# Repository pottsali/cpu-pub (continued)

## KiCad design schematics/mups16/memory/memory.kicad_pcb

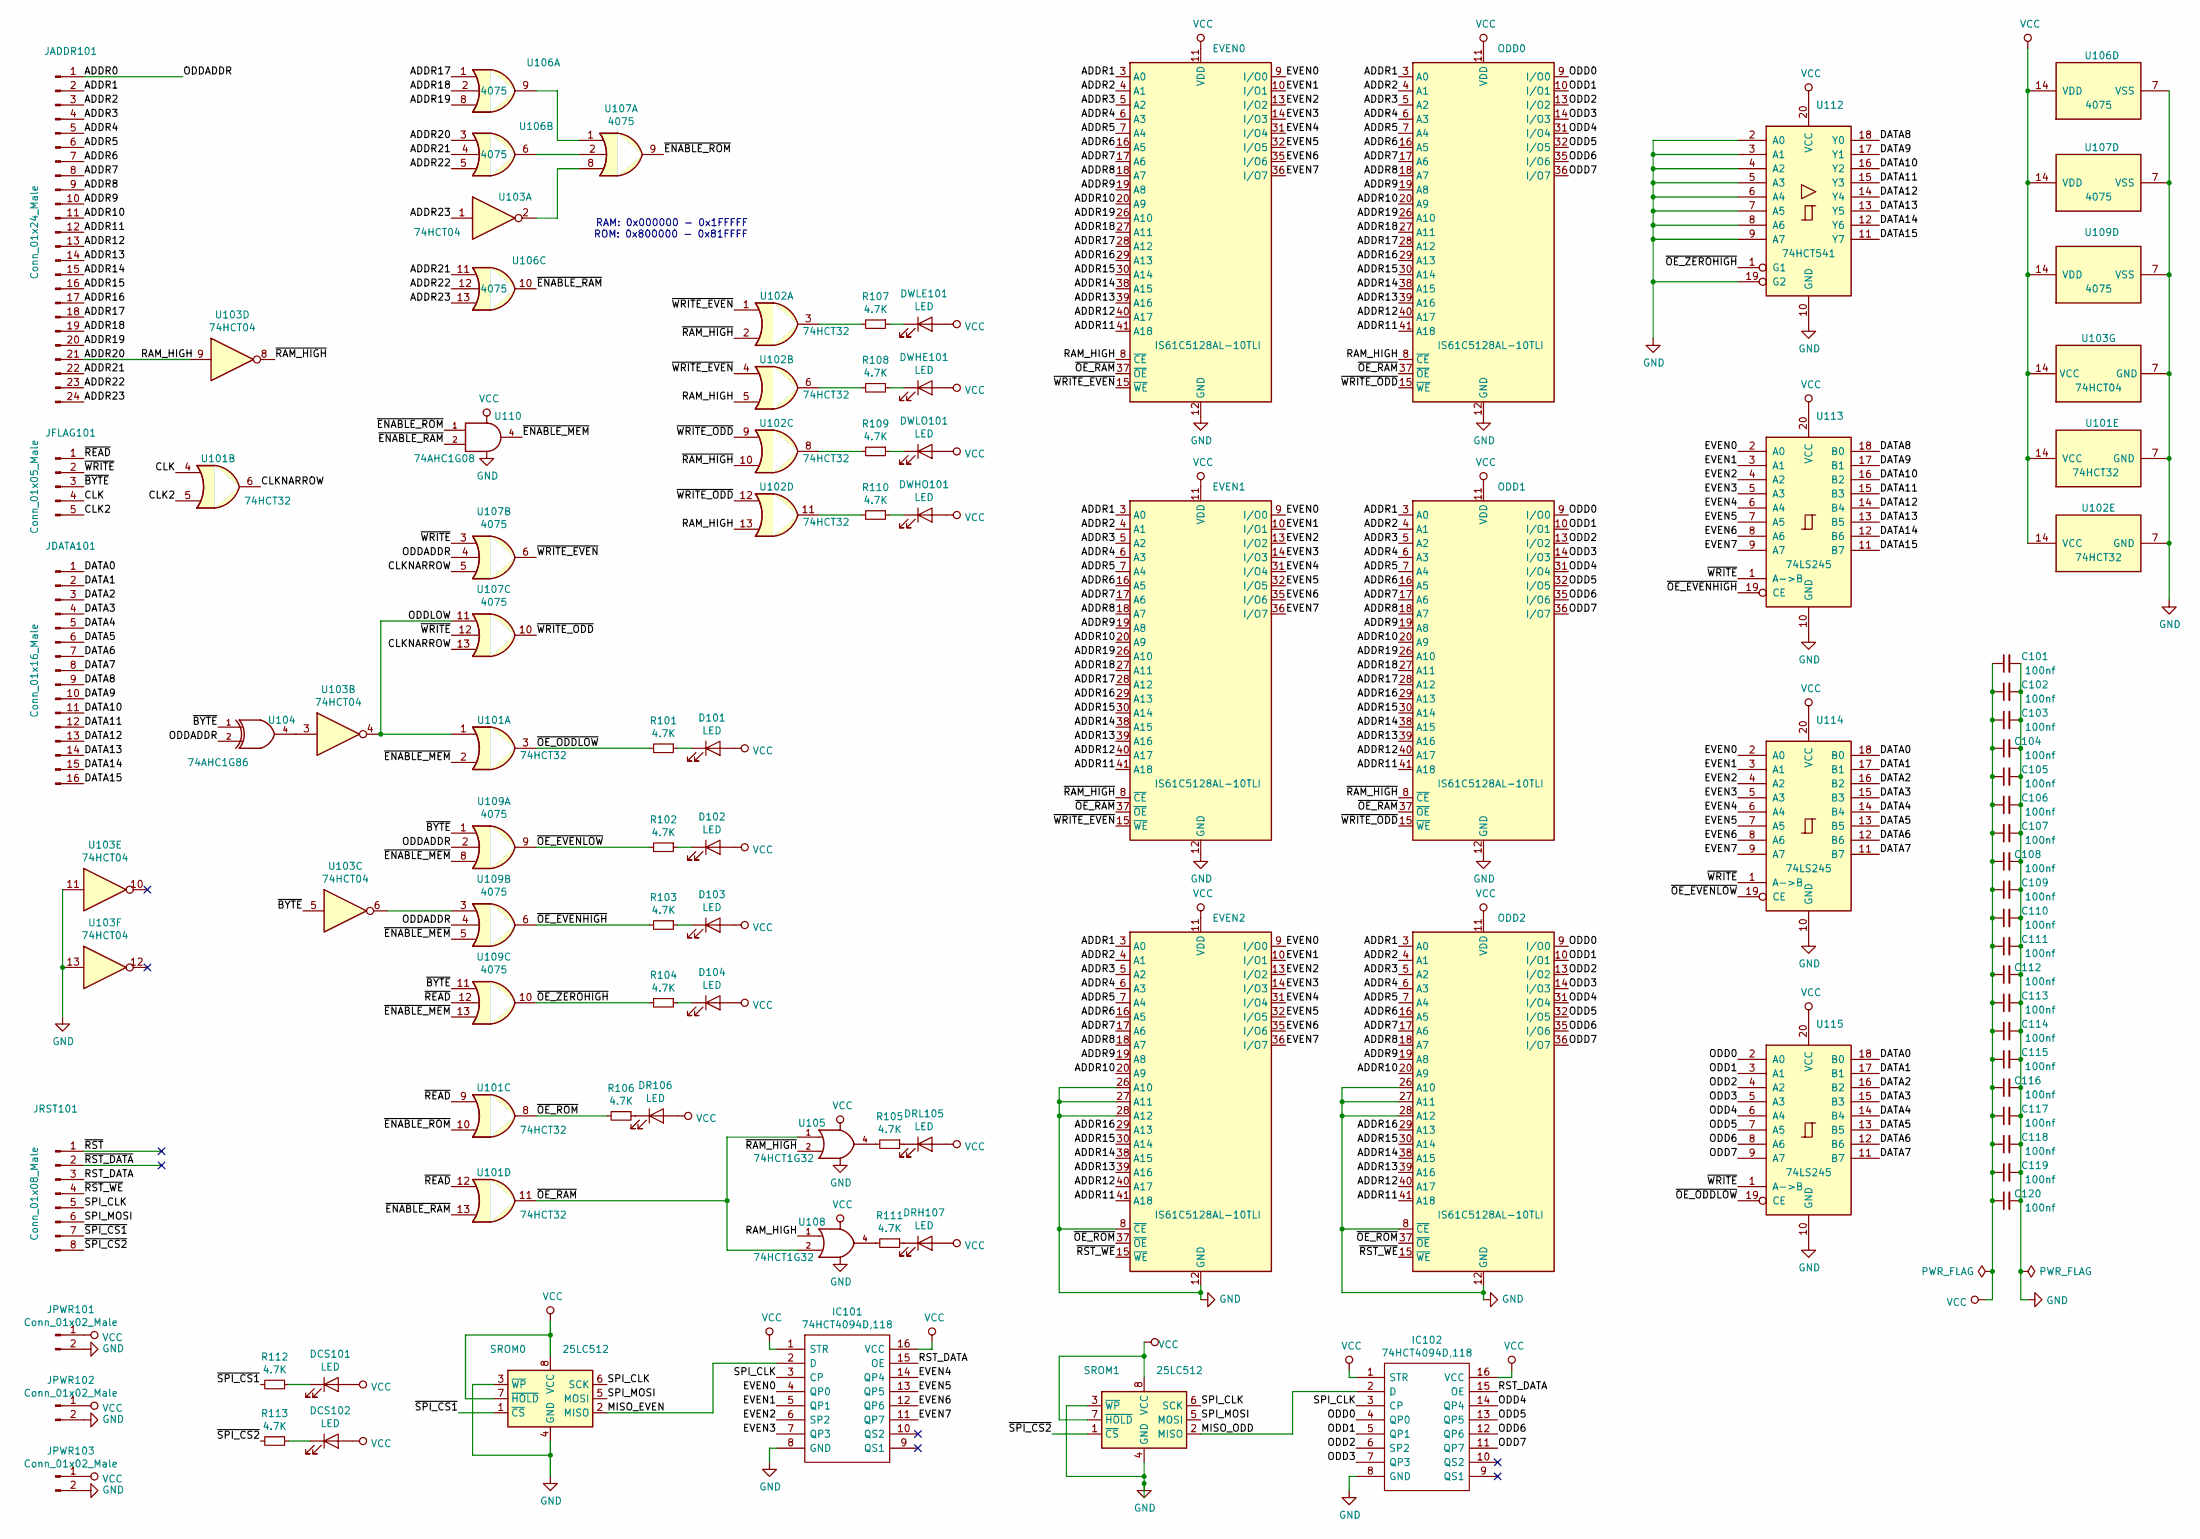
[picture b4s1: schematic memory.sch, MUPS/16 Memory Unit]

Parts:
C101, C102, C103, C104, C105, C106, C107, C108, C109, C110, C111, C112, C113, C114, C115, C116, C117, C118, C119, C120: 100nf; C_0805_2012Metric
D101, D102, D103, D104: LED; LED_0805_2012Metric
DCS101, DCS102: LED; LED_0805_2012Metric
DR106: LED; LED_0805_2012Metric
DRH107: LED; LED_0805_2012Metric
DRL105: LED; LED_0805_2012Metric
DWHE101: LED; LED_0805_2012Metric
DWHO101: LED; LED_0805_2012Metric
DWLE101: LED; LED_0805_2012Metric
DWLO101: LED; LED_0805_2012Metric
EVEN0, EVEN1, EVEN2: IS61C5128AL-10TLI; TSOP-II-44_10.16x18.41mm_P0.8mm
IC101, IC102: 74HCT4094D,118; SOIC127P600X175-16N; Mouser Part Number 771-74HCT4094D-T
JADDR101: Conn_01x24_Male; PinHeader_1x24_P2.54mm_Vertical
JDATA101: Conn_01x16_Male; PinHeader_1x16_P2.54mm_Vertical
JFLAG101: Conn_01x05_Male; PinHeader_1x05_P2.54mm_Vertical
JPWR101, JPWR102, JPWR103: Conn_01x02_Male; PinHeader_1x02_P2.54mm_Vertical
JRST101: Conn_01x08_Male; PinHeader_1x08_P2.54mm_Vertical
ODD0, ODD1, ODD2: IS61C5128AL-10TLI; TSOP-II-44_10.16x18.41mm_P0.8mm
R101, R102, R103, R104, R105, R106, R107, R108, R109, R110, R111, R112, R113: 4.7K; R_0805_2012Metric
SROM0, SROM1: 25LC512; SOIC-8_3.9x4.9mm_P1.27mm
U101, U102: 74HCT32; SOIC-14_3.9x8.7mm_P1.27mm
U103: 74HCT04; SOIC-14_3.9x8.7mm_P1.27mm
U104: 74AHC1G86; TSOP-5_1.65x3.05mm_P0.95mm
U105, U108: 74HCT1G32; TSOP-5_1.65x3.05mm_P0.95mm
U106, U107, U109: 4075; SOIC-14_3.9x8.7mm_P1.27mm
U110: 74AHC1G08; TSOP-5_1.65x3.05mm_P0.95mm
U112: 74HCT541; SO-20_12.8x7.5mm_P1.27mm
U113, U114, U115: 74LS245; SO-20_12.8x7.5mm_P1.27mm

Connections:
/ADDR0: JADDR101.1, U104.2, U107.4, U109.2, U109.4
/ADDR1: EVEN0.3 (A0), EVEN1.3 (A0), EVEN2.3 (A0), JADDR101.2, ODD0.3 (A0), ODD1.3 (A0), ODD2.3 (A0)
/ADDR2: EVEN0.4 (A1), EVEN1.4 (A1), EVEN2.4 (A1), JADDR101.3, ODD0.4 (A1), ODD1.4 (A1), ODD2.4 (A1)
/ADDR3: EVEN0.5 (A2), EVEN1.5 (A2), EVEN2.5 (A2), JADDR101.4, ODD0.5 (A2), ODD1.5 (A2), ODD2.5 (A2)
/ADDR4: EVEN0.6 (A3), EVEN1.6 (A3), EVEN2.6 (A3), JADDR101.5, ODD0.6 (A3), ODD1.6 (A3), ODD2.6 (A3)
/ADDR5: EVEN0.7 (A4), EVEN1.7 (A4), EVEN2.7 (A4), JADDR101.6, ODD0.7 (A4), ODD1.7 (A4), ODD2.7 (A4)
/ADDR6: EVEN0.16 (A5), EVEN1.16 (A5), EVEN2.16 (A5), JADDR101.7, ODD0.16 (A5), ODD1.16 (A5), ODD2.16 (A5)
/ADDR7: EVEN0.17 (A6), EVEN1.17 (A6), EVEN2.17 (A6), JADDR101.8, ODD0.17 (A6), ODD1.17 (A6), ODD2.17 (A6)
/ADDR8: EVEN0.18 (A7), EVEN1.18 (A7), EVEN2.18 (A7), JADDR101.9, ODD0.18 (A7), ODD1.18 (A7), ODD2.18 (A7)
/ADDR9: EVEN0.19 (A8), EVEN1.19 (A8), EVEN2.19 (A8), JADDR101.10, ODD0.19 (A8), ODD1.19 (A8), ODD2.19 (A8)
/ADDR10: EVEN0.20 (A9), EVEN1.20 (A9), EVEN2.20 (A9), JADDR101.11, ODD0.20 (A9), ODD1.20 (A9), ODD2.20 (A9)
/ADDR11: EVEN0.41 (A18), EVEN1.41 (A18), EVEN2.41 (A18), JADDR101.12, ODD0.41 (A18), ODD1.41 (A18), ODD2.41 (A18)
/ADDR12: EVEN0.40 (A17), EVEN1.40 (A17), EVEN2.40 (A17), JADDR101.13, ODD0.40 (A17), ODD1.40 (A17), ODD2.40 (A17)
/ADDR13: EVEN0.39 (A16), EVEN1.39 (A16), EVEN2.39 (A16), JADDR101.14, ODD0.39 (A16), ODD1.39 (A16), ODD2.39 (A16)
/ADDR14: EVEN0.38 (A15), EVEN1.38 (A15), EVEN2.38 (A15), JADDR101.15, ODD0.38 (A15), ODD1.38 (A15), ODD2.38 (A15)
/ADDR15: EVEN0.30 (A14), EVEN1.30 (A14), EVEN2.30 (A14), JADDR101.16, ODD0.30 (A14), ODD1.30 (A14), ODD2.30 (A14)
/ADDR16: EVEN0.29 (A13), EVEN1.29 (A13), EVEN2.29 (A13), JADDR101.17, ODD0.29 (A13), ODD1.29 (A13), ODD2.29 (A13)
/ADDR17: EVEN0.28 (A12), EVEN1.28 (A12), JADDR101.18, ODD0.28 (A12), ODD1.28 (A12), U106.1
/ADDR18: EVEN0.27 (A11), EVEN1.27 (A11), JADDR101.19, ODD0.27 (A11), ODD1.27 (A11), U106.2
/ADDR19: EVEN0.26 (A10), EVEN1.26 (A10), JADDR101.20, ODD0.26 (A10), ODD1.26 (A10), U106.8
/ADDR20: EVEN0.8 (~CE), JADDR101.21, ODD0.8 (~CE), U102.5, U102.13, U103.9, U106.3, U108.1
/ADDR21: JADDR101.22, U106.4, U106.11
/ADDR22: JADDR101.23, U106.5, U106.12
/ADDR23: JADDR101.24, U103.1, U106.13
/CLK: JFLAG101.4, U101.4
/CLK2: JFLAG101.5, U101.5
/CLKNARROW: U101.6, U107.5, U107.13
/DATA0: JDATA101.1, U114.18 (B0), U115.18 (B0)
/DATA1: JDATA101.2, U114.17 (B1), U115.17 (B1)
/DATA2: JDATA101.3, U114.16 (B2), U115.16 (B2)
/DATA3: JDATA101.4, U114.15 (B3), U115.15 (B3)
/DATA4: JDATA101.5, U114.14 (B4), U115.14 (B4)
/DATA5: JDATA101.6, U114.13 (B5), U115.13 (B5)
/DATA6: JDATA101.7, U114.12 (B6), U115.12 (B6)
/DATA7: JDATA101.8, U114.11 (B7), U115.11 (B7)
/DATA8: JDATA101.9, U112.18 (Y0), U113.18 (B0)
/DATA9: JDATA101.10, U112.17 (Y1), U113.17 (B1)
/DATA10: JDATA101.11, U112.16 (Y2), U113.16 (B2)
/DATA11: JDATA101.12, U112.15 (Y3), U113.15 (B3)
/DATA12: JDATA101.13, U112.14 (Y4), U113.14 (B4)
/DATA13: JDATA101.14, U112.13 (Y5), U113.13 (B5)
/DATA14: JDATA101.15, U112.12 (Y6), U113.12 (B6)
/DATA15: JDATA101.16, U112.11 (Y7), U113.11 (B7)
/EVEN0: EVEN0.9 (I/O0), EVEN1.9 (I/O0), EVEN2.9 (I/O0), IC101.4 (QP0), U113.2 (A0), U114.2 (A0)
/EVEN1: EVEN0.10 (I/O1), EVEN1.10 (I/O1), EVEN2.10 (I/O1), IC101.5 (QP1), U113.3 (A1), U114.3 (A1)
/EVEN2: EVEN0.13 (I/O2), EVEN1.13 (I/O2), EVEN2.13 (I/O2), IC101.6 (SP2), U113.4 (A2), U114.4 (A2)
/EVEN3: EVEN0.14 (I/O3), EVEN1.14 (I/O3), EVEN2.14 (I/O3), IC101.7 (QP3), U113.5 (A3), U114.5 (A3)
/EVEN4: EVEN0.31 (I/O4), EVEN1.31 (I/O4), EVEN2.31 (I/O4), IC101.14 (QP4), U113.6 (A4), U114.6 (A4)
/EVEN5: EVEN0.32 (I/O5), EVEN1.32 (I/O5), EVEN2.32 (I/O5), IC101.13 (QP5), U113.7 (A5), U114.7 (A5)
/EVEN6: EVEN0.35 (I/O6), EVEN1.35 (I/O6), EVEN2.35 (I/O6), IC101.12 (QP6), U113.8 (A6), U114.8 (A6)
/EVEN7: EVEN0.36 (I/O7), EVEN1.36 (I/O7), EVEN2.36 (I/O7), IC101.11 (QP7), U113.9 (A7), U114.9 (A7)
/MISO_EVEN: IC101.2 (D), SROM0.2 (MISO)
/MISO_ODD: IC102.2 (D), SROM1.2 (MISO)
/ODD0: IC102.4 (QP0), ODD0.9 (I/O0), ODD1.9 (I/O0), ODD2.9 (I/O0), U115.2 (A0)
/ODD1: IC102.5 (QP1), ODD0.10 (I/O1), ODD1.10 (I/O1), ODD2.10 (I/O1), U115.3 (A1)
/ODD2: IC102.6 (SP2), ODD0.13 (I/O2), ODD1.13 (I/O2), ODD2.13 (I/O2), U115.4 (A2)
/ODD3: IC102.7 (QP3), ODD0.14 (I/O3), ODD1.14 (I/O3), ODD2.14 (I/O3), U115.5 (A3)
/ODD4: IC102.14 (QP4), ODD0.31 (I/O4), ODD1.31 (I/O4), ODD2.31 (I/O4), U115.6 (A4)
/ODD5: IC102.13 (QP5), ODD0.32 (I/O5), ODD1.32 (I/O5), ODD2.32 (I/O5), U115.7 (A5)
/ODD6: IC102.12 (QP6), ODD0.35 (I/O6), ODD1.35 (I/O6), ODD2.35 (I/O6), U115.8 (A6)
/ODD7: IC102.11 (QP7), ODD0.36 (I/O7), ODD1.36 (I/O7), ODD2.36 (I/O7), U115.9 (A7)
/ODDLOW: U101.1, U103.4, U107.11
/RST_DATA: IC101.15 (OE), IC102.15 (OE), JRST101.3
/SPI_CLK: IC101.3 (CP), IC102.3 (CP), JRST101.5, SROM0.6 (SCK), SROM1.6 (SCK)
/SPI_MOSI: JRST101.6, SROM0.5 (MOSI), SROM1.5 (MOSI)
/~: U103.6, U109.3
/~BYTE: JFLAG101.3, U103.5, U104.1, U109.1, U109.11
/~ENABLE_MEM: U101.2, U109.5, U109.8, U109.13, U110.4
/~ENABLE_RAM: U101.13, U106.10, U110.2
/~ENABLE_ROM: U101.10, U107.9, U110.1
/~OE_EVENHIGH: R103.2, U109.6, U113.19 (CE)
/~OE_EVENLOW: R102.2, U109.9, U114.19 (CE)
/~OE_ODDLOW: R101.2, U101.3, U115.19 (CE)
/~OE_RAM: EVEN0.37 (~OE), EVEN1.37 (~OE), ODD0.37 (~OE), ODD1.37 (~OE), U101.11, U105.1, U108.2
/~OE_ROM: EVEN2.37 (~OE), ODD2.37 (~OE), R106.2, U101.8
/~OE_ZEROHIGH: R104.2, U109.10, U112.1 (G1)
/~RAM_HIGH: EVEN1.8 (~CE), ODD1.8 (~CE), U102.2, U102.10, U103.8, U105.2
/~READ: JFLAG101.1, U101.9, U101.12, U109.12
/~RST: JRST101.1
/~RST_DATA: JRST101.2
/~RST_WE: EVEN2.15 (~WE), JRST101.4, ODD2.15 (~WE)
/~SPI_CS1: JRST101.7, R112.2, SROM0.1 (~CS)
/~SPI_CS2: JRST101.8, R113.2, SROM1.1 (~CS)
/~WRITE: JFLAG101.2, U107.3, U107.12, U113.1 (A->B), U114.1 (A->B), U115.1 (A->B)
/~WRITE_EVEN: EVEN0.15 (~WE), EVEN1.15 (~WE), U102.1, U102.4, U107.6
/~WRITE_ODD: ODD0.15 (~WE), ODD1.15 (~WE), U102.9, U102.12, U107.10
GND: C101.2, C102.2, C103.2, C104.2, C105.2, C106.2, C107.2, C108.2, C109.2, C110.2, C111.2, C112.2, C113.2, C114.2, C115.2, C116.2, C117.2, C118.2, C119.2, C120.2, EVEN0.12 (GND), EVEN0.34 (GND), EVEN1.12 (GND), EVEN1.34 (GND), EVEN2.8 (~CE), EVEN2.12 (GND), EVEN2.26 (A10), EVEN2.27 (A11), EVEN2.28 (A12), EVEN2.34 (GND), IC101.8 (GND), IC102.8 (GND), JPWR101.2, JPWR102.2, JPWR103.2, ODD0.12 (GND), ODD0.34 (GND), ODD1.12 (GND), ODD1.34 (GND), ODD2.8 (~CE), ODD2.12 (GND), ODD2.26 (A10), ODD2.27 (A11), ODD2.28 (A12), ODD2.34 (GND), SROM0.3 (~WP), SROM0.4 (GND), SROM1.3 (~WP), SROM1.4 (GND), U101.7 (GND), U102.7 (GND), U103.7 (GND), U103.11, U103.13, U104.3 (GND), U105.3 (GND), U106.7 (VSS), U107.7 (VSS), U108.3 (GND), U109.7 (VSS), U110.3 (GND), U112.2 (A0), U112.3 (A1), U112.4 (A2), U112.5 (A3), U112.6 (A4), U112.7 (A5), U112.8 (A6), U112.9 (A7), U112.10 (GND), U112.19 (G2), U113.10 (GND), U114.10 (GND), U115.10 (GND)
unnamed: D101.1 (K), R101.1
unnamed: D102.1 (K), R102.1
unnamed: D103.1 (K), R103.1
unnamed: D104.1 (K), R104.1
unnamed: DCS101.1 (K), R112.1
unnamed: DCS102.1 (K), R113.1
unnamed: DR106.1 (K), R106.1
unnamed: DRH107.1 (K), R111.1
unnamed: DRL105.1 (K), R105.1
unnamed: DWHE101.1 (K), R108.1
unnamed: DWHO101.1 (K), R110.1
unnamed: DWLE101.1 (K), R107.1
unnamed: DWLO101.1 (K), R109.1
unnamed: R105.2, U105.4
unnamed: R107.2, U102.3
unnamed: R108.2, U102.6
unnamed: R109.2, U102.8
unnamed: R110.2, U102.11
unnamed: R111.2, U108.4
unnamed: U103.2, U107.8
unnamed: U103.3, U104.4
unnamed: U106.6, U107.2
unnamed: U106.9, U107.1
VCC: C101.1, C102.1, C103.1, C104.1, C105.1, C106.1, C107.1, C108.1, C109.1, C110.1, C111.1, C112.1, C113.1, C114.1, C115.1, C116.1, C117.1, C118.1, C119.1, C120.1, D101.2 (A), D102.2 (A), D103.2 (A), D104.2 (A), DCS101.2 (A), DCS102.2 (A), DR106.2 (A), DRH107.2 (A), DRL105.2 (A), DWHE101.2 (A), DWHO101.2 (A), DWLE101.2 (A), DWLO101.2 (A), EVEN0.11 (VDD), EVEN0.33 (VDD), EVEN1.11 (VDD), EVEN1.33 (VDD), EVEN2.11 (VDD), EVEN2.33 (VDD), IC101.1 (STR), IC101.16 (VCC), IC102.1 (STR), IC102.16 (VCC), JPWR101.1, JPWR102.1, JPWR103.1, ODD0.11 (VDD), ODD0.33 (VDD), ODD1.11 (VDD), ODD1.33 (VDD), ODD2.11 (VDD), ODD2.33 (VDD), SROM0.7 (~HOLD), SROM0.8 (VCC), SROM1.7 (~HOLD), SROM1.8 (VCC), U101.14 (VCC), U102.14 (VCC), U103.14 (VCC), U104.5 (VCC), U105.5 (VCC), U106.14 (VDD), U107.14 (VDD), U108.5 (VCC), U109.14 (VDD), U110.5 (VCC), U112.20 (VCC), U113.20 (VCC), U114.20 (VCC), U115.20 (VCC)

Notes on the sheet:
RAM: 0x000000 - 0x1FFFFF ROM: 0x800000 - 0x81FFFF

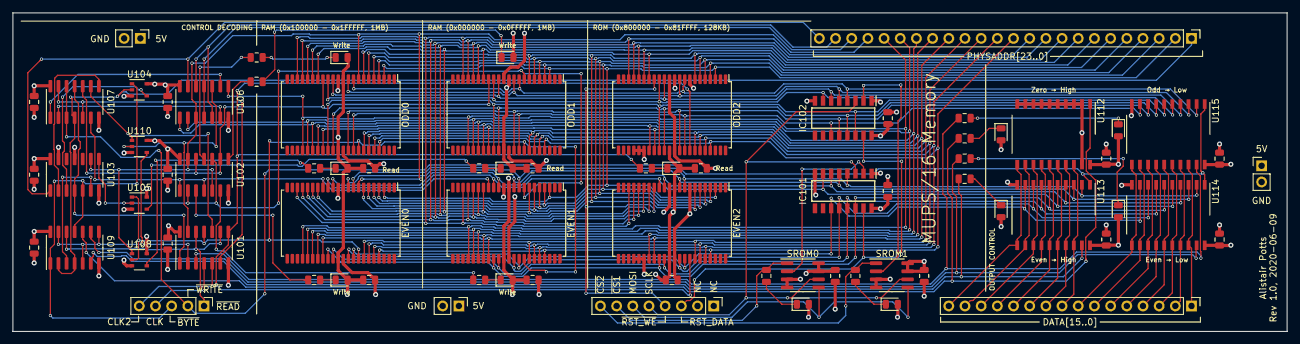
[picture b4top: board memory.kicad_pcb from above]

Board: 4 copper layers, 200.0 x 50.0 mm, 77 parts (0 on the bottom side), 109 nets.

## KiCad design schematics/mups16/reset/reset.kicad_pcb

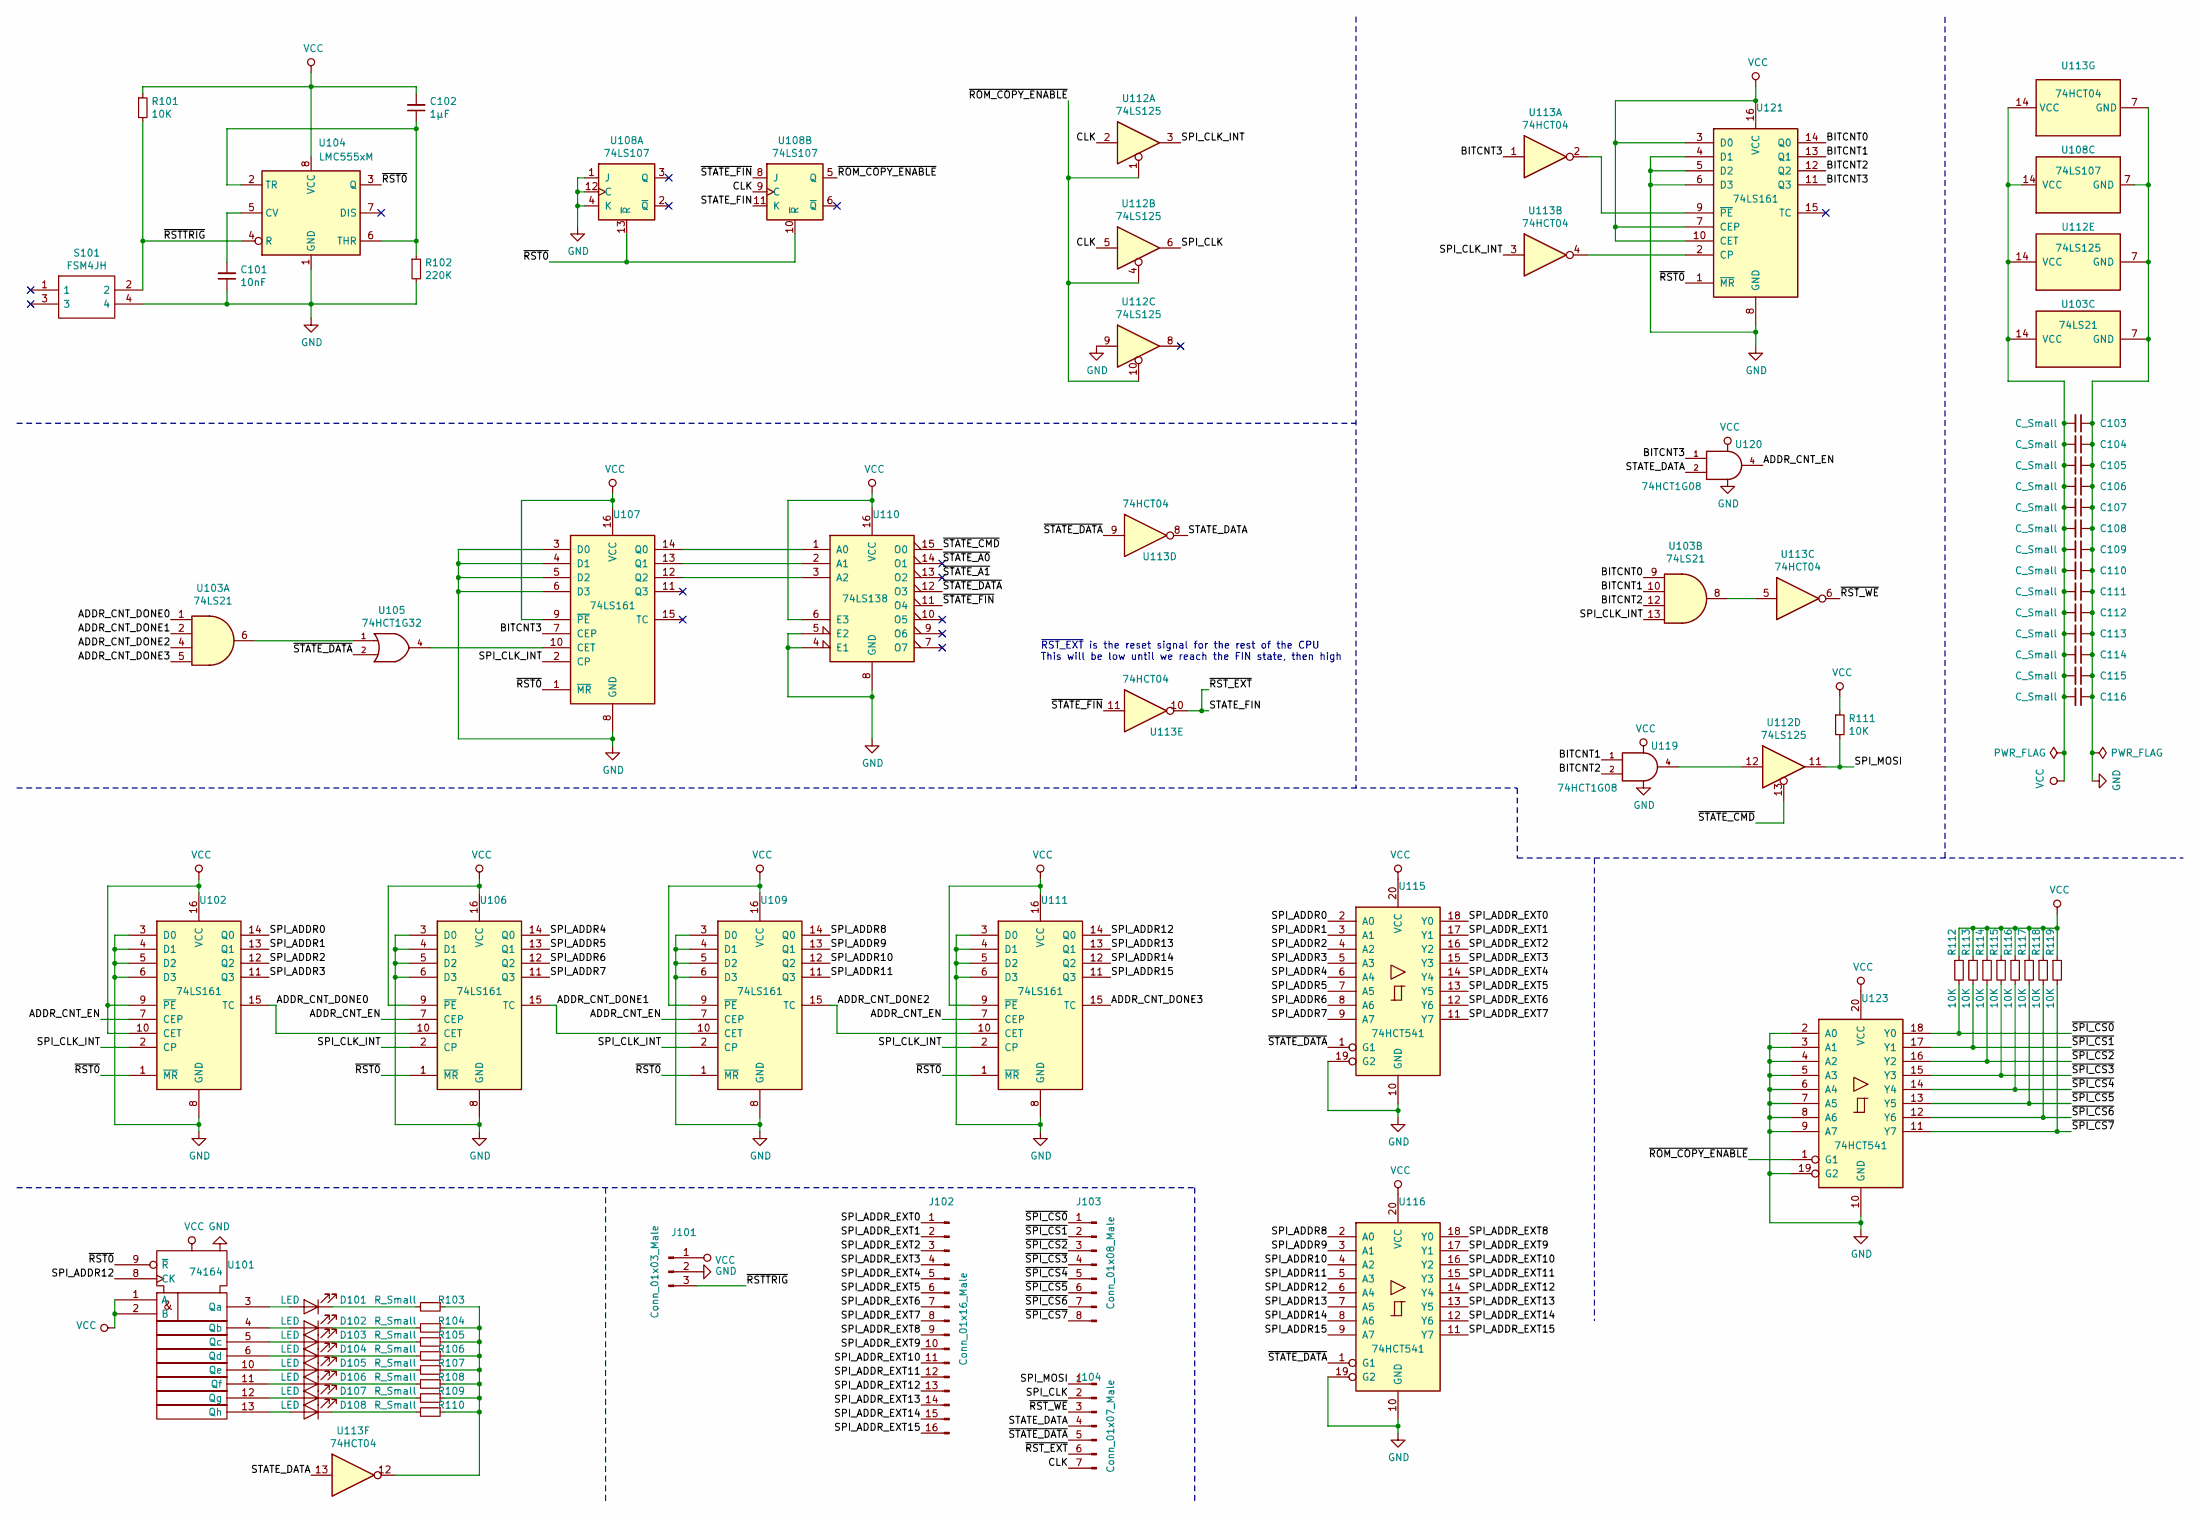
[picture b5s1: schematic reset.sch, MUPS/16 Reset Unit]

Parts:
C101: 10nF; C_0805_2012Metric
C102: 1μF; C_0805_2012Metric
C103, C104, C105, C106, C107, C108, C109, C110, C111, C112, C113, C114, C115, C116: C_Small; C_0805_2012Metric
D101, D102, D103, D104, D105, D106, D107, D108: LED; LED_0805_2012Metric
J101: Conn_01x03_Male; PinHeader_1x03_P2.54mm_Vertical
J102: Conn_01x16_Male; PinHeader_1x16_P2.54mm_Vertical
J103: Conn_01x08_Male; PinHeader_1x08_P2.54mm_Vertical
J104: Conn_01x07_Male; PinHeader_1x07_P2.54mm_Vertical
R101, R111, R112, R113, R114, R115, R116, R117, R118, R119: 10K; R_0805_2012Metric
R102: 220K; R_0805_2012Metric
R103, R104, R105, R106, R107, R108, R109, R110: R_Small; R_0805_2012Metric
S101: FSM4JH; Mouser Part Number 506-FSM4JH
U101: 74164; SOIC-14_3.9x8.7mm_P1.27mm
U102, U106, U107, U109, U111, U121: 74LS161; SOIC-16_3.9x9.9mm_P1.27mm
U103: 74LS21; SOIC-14_3.9x8.7mm_P1.27mm
U104: LMC555xM; SOIC-8_3.9x4.9mm_P1.27mm
U105: 74HCT1G32; TSOP-5_1.65x3.05mm_P0.95mm
U108: 74LS107; SOIC-14_3.9x8.7mm_P1.27mm
U110: 74LS138; SOIC-16_3.9x9.9mm_P1.27mm
U112: 74LS125; SOIC-14_3.9x8.7mm_P1.27mm
U113: 74HCT04; SOIC-14_3.9x8.7mm_P1.27mm
U115, U116, U123: 74HCT541; SO-20_12.8x7.5mm_P1.27mm
U119, U120: 74HCT1G08; TSOP-5_1.65x3.05mm_P0.95mm

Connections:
/ADDR_CNT_DONE0: U102.15 (TC), U103.1, U106.10 (CET)
/ADDR_CNT_DONE1: U103.2, U106.15 (TC), U109.10 (CET)
/ADDR_CNT_DONE2: U103.4, U109.15 (TC), U111.10 (CET)
/ADDR_CNT_DONE3: U103.5, U111.15 (TC)
/ADDR_CNT_EN: U102.7 (CEP), U106.7 (CEP), U109.7 (CEP), U111.7 (CEP), U120.4
/BITCNT0: U103.9, U121.14 (Q0)
/BITCNT1: U103.10, U119.1, U121.13 (Q1)
/BITCNT2: U103.12, U119.2, U121.12 (Q2)
/BITCNT3: U107.7 (CEP), U113.1, U120.1, U121.11 (Q3)
/CLK: J104.7, U108.9 (C), U112.2, U112.5
/SPI_ADDR0: U102.14 (Q0), U115.2 (A0)
/SPI_ADDR1: U102.13 (Q1), U115.3 (A1)
/SPI_ADDR2: U102.12 (Q2), U115.4 (A2)
/SPI_ADDR3: U102.11 (Q3), U115.5 (A3)
/SPI_ADDR4: U106.14 (Q0), U115.6 (A4)
/SPI_ADDR5: U106.13 (Q1), U115.7 (A5)
/SPI_ADDR6: U106.12 (Q2), U115.8 (A6)
/SPI_ADDR7: U106.11 (Q3), U115.9 (A7)
/SPI_ADDR8: U109.14 (Q0), U116.2 (A0)
/SPI_ADDR9: U109.13 (Q1), U116.3 (A1)
/SPI_ADDR10: U109.12 (Q2), U116.4 (A2)
/SPI_ADDR11: U109.11 (Q3), U116.5 (A3)
/SPI_ADDR12: U101.8 (CK), U111.14 (Q0), U116.6 (A4)
/SPI_ADDR13: U111.13 (Q1), U116.7 (A5)
/SPI_ADDR14: U111.12 (Q2), U116.8 (A6)
/SPI_ADDR15: U111.11 (Q3), U116.9 (A7)
/SPI_ADDR_EXT0: J102.1, U115.18 (Y0)
/SPI_ADDR_EXT1: J102.2, U115.17 (Y1)
/SPI_ADDR_EXT2: J102.3, U115.16 (Y2)
/SPI_ADDR_EXT3: J102.4, U115.15 (Y3)
/SPI_ADDR_EXT4: J102.5, U115.14 (Y4)
/SPI_ADDR_EXT5: J102.6, U115.13 (Y5)
/SPI_ADDR_EXT6: J102.7, U115.12 (Y6)
/SPI_ADDR_EXT7: J102.8, U115.11 (Y7)
/SPI_ADDR_EXT8: J102.9, U116.18 (Y0)
/SPI_ADDR_EXT9: J102.10, U116.17 (Y1)
/SPI_ADDR_EXT10: J102.11, U116.16 (Y2)
/SPI_ADDR_EXT11: J102.12, U116.15 (Y3)
/SPI_ADDR_EXT12: J102.13, U116.14 (Y4)
/SPI_ADDR_EXT13: J102.14, U116.13 (Y5)
/SPI_ADDR_EXT14: J102.15, U116.12 (Y6)
/SPI_ADDR_EXT15: J102.16, U116.11 (Y7)
/SPI_CLK: J104.2, U112.6
/SPI_CLK_INT: U102.2 (CP), U103.13, U106.2 (CP), U107.2 (CP), U109.2 (CP), U111.2 (CP), U112.3, U113.3
/SPI_MOSI: J104.1, R111.2, U112.11
/STATE_DATA: J104.4, U113.8, U113.13, U120.2
/STATE_FIN: J104.6, U108.11 (K), U113.10
/~ROM_COPY_ENABLE: U108.5 (Q), U112.1, U112.4, U112.10, U123.1 (G1)
/~RST0: U101.9 (~R), U102.1 (~MR), U104.3 (Q), U106.1 (~MR), U107.1 (~MR), U108.10 (~R), U108.13 (~R), U109.1 (~MR), U111.1 (~MR), U121.1 (~MR)
/~RSTTRIG: J101.3, R101.2, S101.2, U104.4 (R)
/~RST_WE: J104.3, U113.6
/~SPI_CS0: J103.1, R112.2, U123.18 (Y0)
/~SPI_CS1: J103.2, R113.2, U123.17 (Y1)
/~SPI_CS2: J103.3, R114.2, U123.16 (Y2)
/~SPI_CS3: J103.4, R115.2, U123.15 (Y3)
/~SPI_CS4: J103.5, R116.2, U123.14 (Y4)
/~SPI_CS5: J103.6, R117.2, U123.13 (Y5)
/~SPI_CS6: J103.7, R118.2, U123.12 (Y6)
/~SPI_CS7: J103.8, R119.2, U123.11 (Y7)
/~STATE_A0: U110.14 (O1)
/~STATE_A1: U110.13 (O2)
/~STATE_CMD: U110.15 (O0), U112.13
/~STATE_DATA: J104.5, U105.2, U110.12 (O3), U113.9, U115.1 (G1), U116.1 (G1)
/~STATE_FIN: U108.8 (J), U110.11 (O4), U113.11
GND: C101.1, C103.1, C104.1, C105.1, C106.1, C107.1, C108.1, C109.1, C110.1, C111.1, C112.1, C113.1, C114.1, C115.1, C116.1, J101.2, R102.2, S101.4, U101.14 (Vdd), U102.3 (D0), U102.4 (D1), U102.5 (D2), U102.6 (D3), U102.8 (GND), U103.7 (GND), U104.1 (GND), U105.3 (GND), U106.3 (D0), U106.4 (D1), U106.5 (D2), U106.6 (D3), U106.8 (GND), U107.3 (D0), U107.4 (D1), U107.5 (D2), U107.6 (D3), U107.8 (GND), U108.1 (J), U108.4 (K), U108.7 (GND), U108.12 (C), U109.3 (D0), U109.4 (D1), U109.5 (D2), U109.6 (D3), U109.8 (GND), U110.4 (E1), U110.5 (E2), U110.8 (GND), U111.3 (D0), U111.4 (D1), U111.5 (D2), U111.6 (D3), U111.8 (GND), U112.7 (GND), U112.9, U113.7 (GND), U115.10 (GND), U115.19 (G2), U116.10 (GND), U116.19 (G2), U119.3 (GND), U120.3 (GND), U121.4 (D1), U121.5 (D2), U121.6 (D3), U121.8 (GND), U123.2 (A0), U123.3 (A1), U123.4 (A2), U123.5 (A3), U123.6 (A4), U123.7 (A5), U123.8 (A6), U123.9 (A7), U123.10 (GND), U123.19 (G2)
unnamed: C101.2, U104.5 (CV)
unnamed: C102.1, R102.1, U104.2 (TR), U104.6 (THR)
unnamed: D101.1 (K), R103.2
unnamed: D101.2 (A), U101.3 (Qa)
unnamed: D102.1 (K), R104.2
unnamed: D102.2 (A), U101.4 (Qb)
unnamed: D103.1 (K), R105.2
unnamed: D103.2 (A), U101.5 (Qc)
unnamed: D104.1 (K), R106.2
unnamed: D104.2 (A), U101.6 (Qd)
unnamed: D105.1 (K), R107.2
unnamed: D105.2 (A), U101.10 (Qe)
unnamed: D106.1 (K), R108.2
unnamed: D106.2 (A), U101.11 (Qf)
unnamed: D107.1 (K), R109.2
unnamed: D107.2 (A), U101.12 (Qg)
unnamed: D108.1 (K), R110.2
unnamed: D108.2 (A), U101.13 (Qh)
unnamed: R103.1, R104.1, R105.1, R106.1, R107.1, R108.1, R109.1, R110.1, U113.12
unnamed: U103.6, U105.1
unnamed: U103.8, U113.5
unnamed: U105.4, U107.10 (CET)
unnamed: U107.12 (Q2), U110.3 (A2)
unnamed: U107.13 (Q1), U110.2 (A1)
unnamed: U107.14 (Q0), U110.1 (A0)
unnamed: U112.12, U119.4
unnamed: U113.2, U121.9 (~PE)
unnamed: U113.4, U121.2 (CP)
VCC: C102.2, C103.2, C104.2, C105.2, C106.2, C107.2, C108.2, C109.2, C110.2, C111.2, C112.2, C113.2, C114.2, C115.2, C116.2, J101.1, R101.1, R111.1, R112.1, R113.1, R114.1, R115.1, R116.1, R117.1, R118.1, R119.1, U101.1 (A), U101.2 (B), U101.7 (Vss), U102.9 (~PE), U102.10 (CET), U102.16 (VCC), U103.14 (VCC), U104.8 (VCC), U105.5 (VCC), U106.9 (~PE), U106.16 (VCC), U107.9 (~PE), U107.16 (VCC), U108.14 (VCC), U109.9 (~PE), U109.16 (VCC), U110.6 (E3), U110.16 (VCC), U111.9 (~PE), U111.16 (VCC), U112.14 (VCC), U113.14 (VCC), U115.20 (VCC), U116.20 (VCC), U119.5 (VCC), U120.5 (VCC), U121.3 (D0), U121.7 (CEP), U121.10 (CET), U121.16 (VCC), U123.20 (VCC)

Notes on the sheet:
~RST_EXT~ is the reset signal for the rest of the CPU This will be low until we reach the FIN state, then high

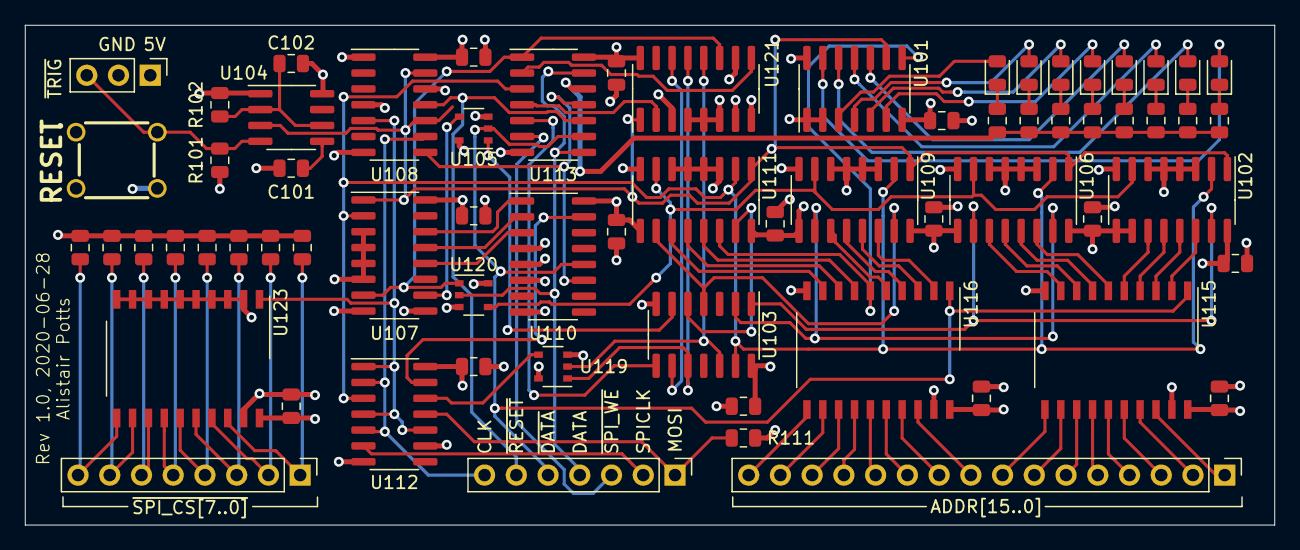
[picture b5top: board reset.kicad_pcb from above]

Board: 4 copper layers, 100.0 x 40.0 mm, 67 parts (0 on the bottom side), 92 nets.

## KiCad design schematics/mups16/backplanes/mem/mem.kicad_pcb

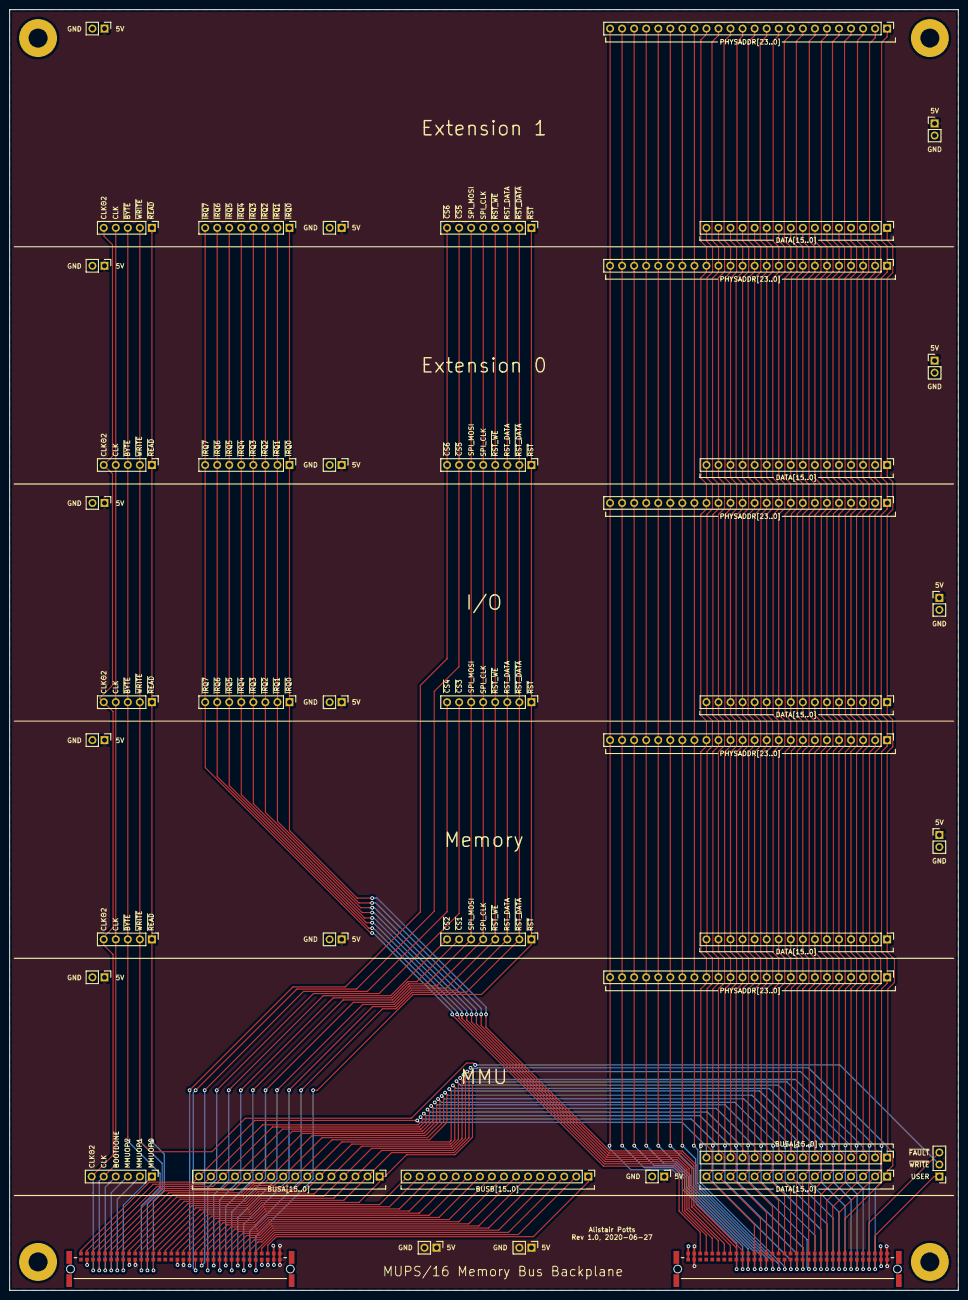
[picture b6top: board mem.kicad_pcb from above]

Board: 2 copper layers, 200.0 x 270.0 mm, 48 parts (0 on the bottom side), 105 nets.

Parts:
J101, J102, J106, J121, J128, J135, J142: Conn_01x08_Male; PinHeader_1x08_P2.54mm_Vertical
J103, J109, J113, J114, J115, J118, J125, J132: Conn_01x16_Male; PinHeader_1x16_P2.54mm_Vertical
J104, J110, J119, J126, J133: Conn_01x24_Male; PinHeader_1x24_P2.54mm_Vertical
J105, J120, J127, J134: Conn_01x05_Male; PinHeader_1x05_P2.54mm_Vertical
J107, J108, J116, J117, J122, J123, J124, J129, J130, J131, J136, J137, J138, J141, J147, J148: Conn_01x02_Male; PinHeader_1x02_P2.54mm_Vertical
J111: Conn_01x06_Male; PinHeader_1x06_P2.54mm_Vertical
J112: Conn_01x03_Male; PinHeader_1x03_P2.54mm_Vertical
J139, J140: M55-6106842R; M556106842R
J143, J144, J145, J146: Conn_01x01_Male; MountingHole_4mm_Pad

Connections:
/BOOTDONE: J111.4, J139.64
/BUSA0: J113.1, J115.1, J139.19
/BUSA1: J113.2, J115.2, J139.20
/BUSA2: J113.3, J115.3, J139.21
/BUSA3: J113.4, J115.4, J139.22
/BUSA4: J113.5, J115.5, J139.23
/BUSA5: J113.6, J115.6, J139.24
/BUSA6: J113.7, J115.7, J139.25
/BUSA7: J113.8, J115.8, J139.26
/BUSA8: J113.9, J115.9, J139.27
/BUSA9: J113.10, J115.10, J139.28
/BUSA10: J113.11, J115.11, J139.29
/BUSA11: J113.12, J115.12, J139.30
/BUSA12: J113.13, J115.13, J139.31
/BUSA13: J113.14, J115.14, J139.32
/BUSA14: J113.15, J115.15, J139.33
/BUSA15: J113.16, J115.16, J139.34
/BUSB0: J114.1, J139.3
/BUSB1: J114.2, J139.4
/BUSB2: J114.3, J139.5
/BUSB3: J114.4, J139.6
/BUSB4: J114.5, J139.7
/BUSB5: J114.6, J139.8
/BUSB6: J114.7, J139.9
/BUSB7: J114.8, J139.10
/BUSB8: J114.9, J139.11
/BUSB9: J114.10, J139.12
/BUSB10: J114.11, J139.13
/BUSB11: J114.12, J139.14
/BUSB12: J114.13, J139.15
/BUSB13: J114.14, J139.16
/BUSB14: J114.15, J139.17
/BUSB15: J114.16, J139.18
/CLK: J105.4, J111.5, J120.4, J127.4, J134.4, J139.65
/CLK2: J105.5, J111.6, J120.5, J127.5, J134.5, J139.66
/DATA0: J103.1, J109.1, J118.1, J125.1, J132.1, J140.8
/DATA1: J103.2, J109.2, J118.2, J125.2, J132.2, J140.9
/DATA2: J103.3, J109.3, J118.3, J125.3, J132.3, J140.10
/DATA3: J103.4, J109.4, J118.4, J125.4, J132.4, J140.11
/DATA4: J103.5, J109.5, J118.5, J125.5, J132.5, J140.12
/DATA5: J103.6, J109.6, J118.6, J125.6, J132.6, J140.13
/DATA6: J103.7, J109.7, J118.7, J125.7, J132.7, J140.14
/DATA7: J103.8, J109.8, J118.8, J125.8, J132.8, J140.15
/DATA8: J103.9, J109.9, J118.9, J125.9, J132.9, J140.16
/DATA9: J103.10, J109.10, J118.10, J125.10, J132.10, J140.17
/DATA10: J103.11, J109.11, J118.11, J125.11, J132.11, J140.18
/DATA11: J103.12, J109.12, J118.12, J125.12, J132.12, J140.19
/DATA12: J103.13, J109.13, J118.13, J125.13, J132.13, J140.20
/DATA13: J103.14, J109.14, J118.14, J125.14, J132.14, J140.21
/DATA14: J103.15, J109.15, J118.15, J125.15, J132.15, J140.22
/DATA15: J103.16, J109.16, J118.16, J125.16, J132.16, J140.23
/MMUOP0: J111.1, J139.61
/MMUOP1: J111.2, J139.62
/MMUOP2: J111.3, J139.63
/PHYSADDR0: J104.1, J110.1, J119.1, J126.1, J133.1, J140.37
/PHYSADDR1: J104.2, J110.2, J119.2, J126.2, J133.2, J140.38
/PHYSADDR2: J104.3, J110.3, J119.3, J126.3, J133.3, J140.39
/PHYSADDR3: J104.4, J110.4, J119.4, J126.4, J133.4, J140.40
/PHYSADDR4: J104.5, J110.5, J119.5, J126.5, J133.5, J140.41
/PHYSADDR5: J104.6, J110.6, J119.6, J126.6, J133.6, J140.42
/PHYSADDR6: J104.7, J110.7, J119.7, J126.7, J133.7, J140.43
/PHYSADDR7: J104.8, J110.8, J119.8, J126.8, J133.8, J140.44
/PHYSADDR8: J104.9, J110.9, J119.9, J126.9, J133.9, J140.45
/PHYSADDR9: J104.10, J110.10, J119.10, J126.10, J133.10, J140.46
/PHYSADDR10: J104.11, J110.11, J119.11, J126.11, J133.11, J140.47
/PHYSADDR11: J104.12, J110.12, J119.12, J126.12, J133.12, J140.48
/PHYSADDR12: J104.13, J110.13, J119.13, J126.13, J133.13, J140.49
/PHYSADDR13: J104.14, J110.14, J119.14, J126.14, J133.14, J140.50
/PHYSADDR14: J104.15, J110.15, J119.15, J126.15, J133.15, J140.51
/PHYSADDR15: J104.16, J110.16, J119.16, J126.16, J133.16, J140.52
/PHYSADDR16: J104.17, J110.17, J119.17, J126.17, J133.17, J140.53
/PHYSADDR17: J104.18, J110.18, J119.18, J126.18, J133.18, J140.54
/PHYSADDR18: J104.19, J110.19, J119.19, J126.19, J133.19, J140.55
/PHYSADDR19: J104.20, J110.20, J119.20, J126.20, J133.20, J140.56
/PHYSADDR20: J104.21, J110.21, J119.21, J126.21, J133.21, J140.57
/PHYSADDR21: J104.22, J110.22, J119.22, J126.22, J133.22, J140.58
/PHYSADDR22: J104.23, J110.23, J119.23, J126.23, J133.23, J140.59
/PHYSADDR23: J104.24, J110.24, J119.24, J126.24, J133.24, J140.60
/RST_DATA: J106.3, J121.3, J128.3, J135.3, J139.41
/SPI_CLK: J106.5, J121.5, J128.5, J135.5, J139.43
/SPI_MOSI: J106.6, J121.6, J128.6, J135.6, J139.44
/USER: J112.1, J140.3
/~BYTE: J105.3, J120.3, J127.3, J134.3, J139.58
/~FAULT: J112.3, J140.4
/~IRQ0: J101.1, J102.1, J140.25, J142.1
/~IRQ1: J101.2, J102.2, J140.26, J142.2
/~IRQ2: J101.3, J102.3, J140.27, J142.3
/~IRQ3: J101.4, J102.4, J140.28, J142.4
/~IRQ4: J101.5, J102.5, J140.29, J142.5
/~IRQ5: J101.6, J102.6, J140.30, J142.6
/~IRQ6: J101.7, J102.7, J140.31, J142.7
/~IRQ7: J101.8, J102.8, J140.32, J142.8
/~READ: J105.1, J120.1, J127.1, J134.1, J139.56
/~RST: J106.1, J121.1, J128.1, J135.1, J139.39
/~RST_DATA: J106.2, J121.2, J128.2, J135.2, J139.40
/~RST_WE: J106.4, J121.4, J128.4, J135.4, J139.42
/~SPI_CS1: J121.7, J139.45
/~SPI_CS2: J121.8, J139.46
/~SPI_CS3: J128.7, J139.47
/~SPI_CS4: J128.8, J139.48
/~SPI_CS5: J106.7, J135.7, J139.49
/~SPI_CS6: J106.8, J135.8, J139.50
/~WRITE: J105.2, J112.2, J120.2, J127.2, J134.2, J139.57
GND: J107.2, J108.2, J116.2, J117.2, J122.2, J123.2, J124.2, J129.2, J130.2, J131.2, J136.2, J137.2, J138.2, J139.2, J139.36, J139.38, J139.52, J139.60, J140.2, J140.34, J140.36, J140.68, J141.2, J147.2, J148.2
VCC: J107.1, J108.1, J116.1, J117.1, J122.1, J123.1, J124.1, J129.1, J130.1, J131.1, J136.1, J137.1, J138.1, J139.1, J139.35, J139.37, J139.51, J139.59, J140.1, J140.33, J140.35, J140.67, J141.1, J147.1, J148.1
